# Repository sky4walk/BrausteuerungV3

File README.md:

# BrausteuerungV3
mikroSikaru.de

brausteuerung@AndreBetz.de
 
more Information found on 
https://zwieselbrau.wordpress.com/2016/03/30/mikrosikaru-brausteuerung-v3-bluetooth/

Video Tutorial
https://zwieselbrau.wordpress.com/2017/05/13/mikrosikaru-brausteuerung-v3-bedienung-videoanleitung/

Android App in Playstore:
https://play.google.com/store/apps/details?id=de.mikrosikaru.brausteuerungapp

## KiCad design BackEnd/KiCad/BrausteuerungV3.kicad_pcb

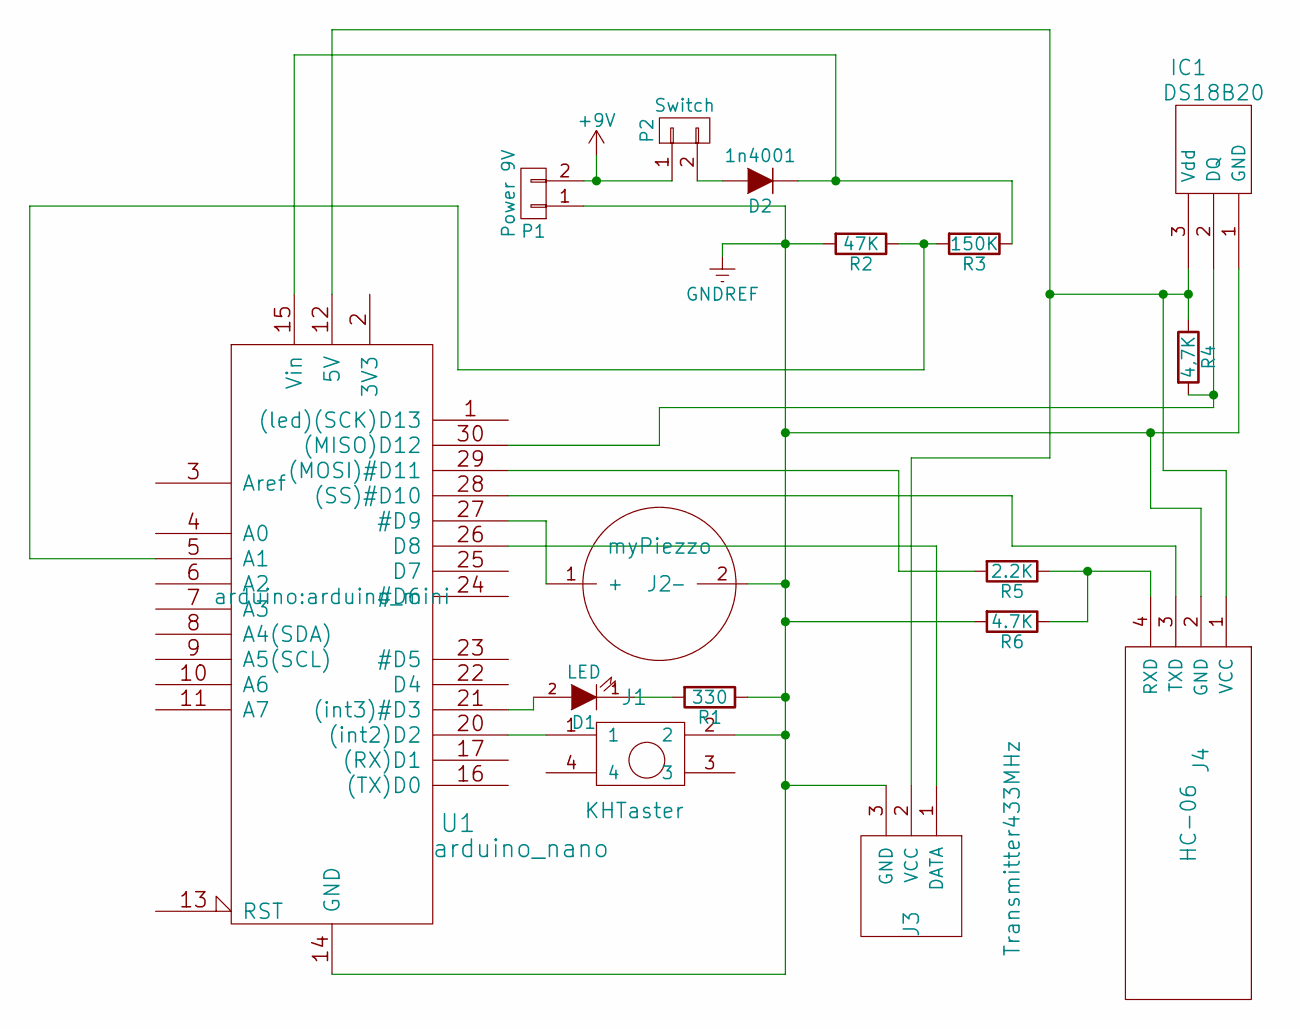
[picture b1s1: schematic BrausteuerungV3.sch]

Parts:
D1: LED; R_Axial_DIN0204_L3.6mm_D1.6mm_P1.90mm_Vertical
D2: 1n4001; R_Axial_DIN0207_L6.3mm_D2.5mm_P10.16mm_Horizontal
IC1: DS18B20
J1: KHTaster
J2: myPiezzo; PIEZZO
J3: Transmitter433MHz
J4: HC-06
P1: Power 9V; R_Axial_DIN0204_L3.6mm_D1.6mm_P1.90mm_Vertical
P2: Switch; R_Axial_DIN0204_L3.6mm_D1.6mm_P1.90mm_Vertical
R1: 330; R_Axial_DIN0207_L6.3mm_D2.5mm_P10.16mm_Horizontal
R2: 47K; R_Axial_DIN0207_L6.3mm_D2.5mm_P10.16mm_Horizontal
R3: 150K; R_Axial_DIN0207_L6.3mm_D2.5mm_P10.16mm_Horizontal
R4: 4,7K; R_Axial_DIN0207_L6.3mm_D2.5mm_P10.16mm_Horizontal
R5: 2.2K; R_Axial_DIN0207_L6.3mm_D2.5mm_P10.16mm_Horizontal
R6: 4.7K; R_Axial_DIN0207_L6.3mm_D2.5mm_P10.16mm_Horizontal
U1: arduino_nano; arduino_mini

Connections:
+9V: P1.2, P2.1
GND: U1.19 (GND)
GNDREF: IC1.1 (GND), J1.2, J2.2 (-), J3.3 (GND), J4.2 (GND), P1.1, R1.1, R2.2, R6.2, U1.14 (GND)
unnamed: D1.1 (K), R1.2
unnamed: D1.2 (A), U1.21 ((int3)#D3)
unnamed: D2.1 (K), R3.1, U1.15 (Vin)
unnamed: D2.2 (A), P2.2
unnamed: IC1.2 (DQ), R4.2, U1.30 ((MISO)D12)
unnamed: IC1.3 (Vdd), J3.2 (VCC), J4.1 (VCC), R4.1, U1.12 (5V)
unnamed: J1.1, U1.20 ((int2)D2)
unnamed: J2.1 (+), U1.27 (#D9)
unnamed: J3.1 (DATA), U1.26 (D8)
unnamed: J4.3 (TXD), U1.28 ((SS)#D10)
unnamed: J4.4 (RXD), R5.1, R6.1
unnamed: R2.1, R3.2, U1.5 (A1)
unnamed: R5.2, U1.29 ((MOSI)#D11)

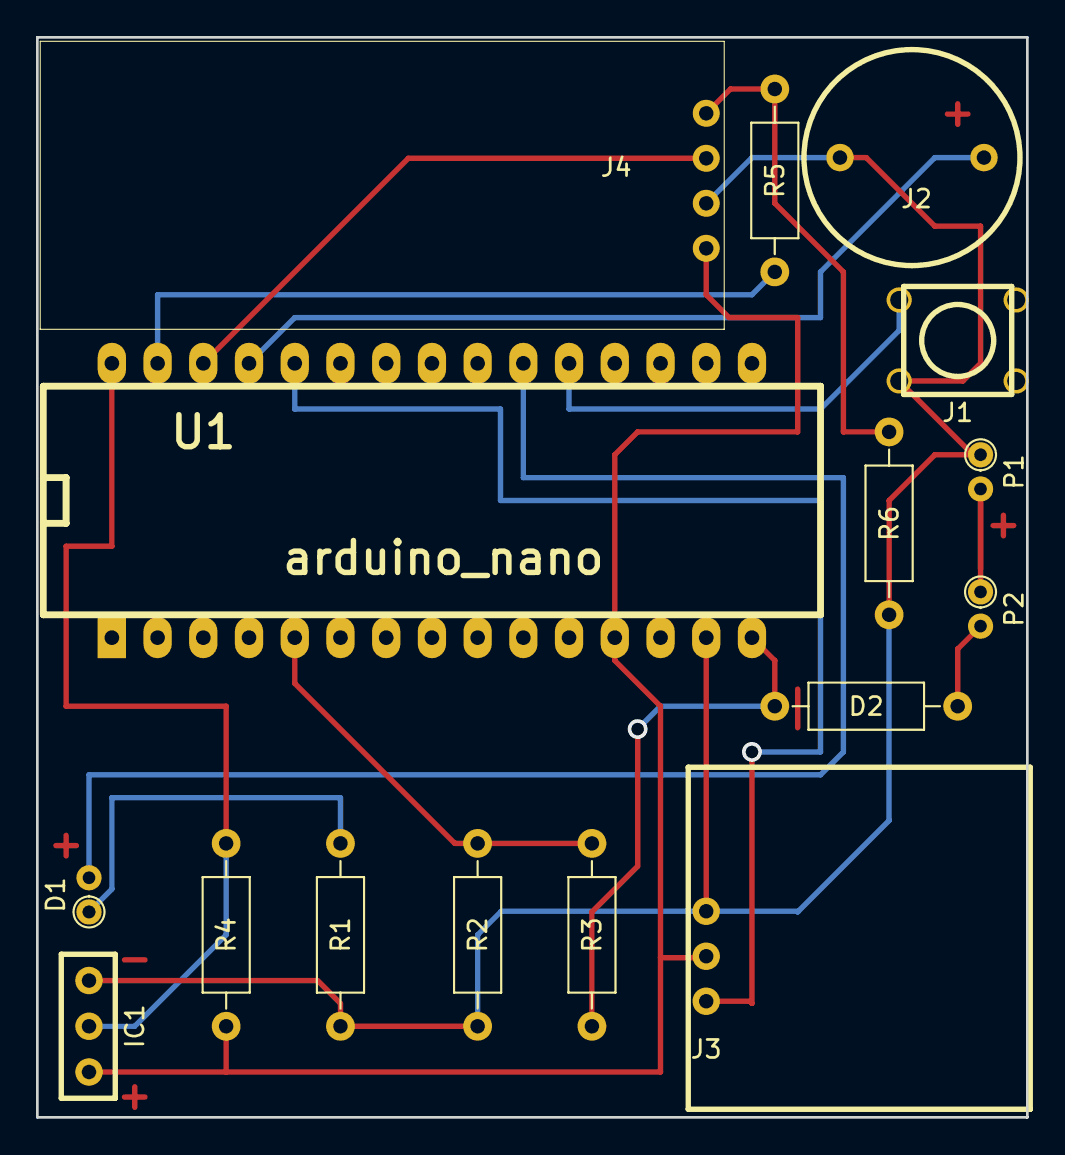
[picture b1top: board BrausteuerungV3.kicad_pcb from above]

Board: 2 copper layers, 55.0 x 60.0 mm, 16 parts (0 on the bottom side), 15 nets.

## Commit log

2016-04-25 Start BrausteuerungV3 checkin
2016-04-25 Bier Rezepte und Manual
2016-04-25 Android App
2016-04-26 version 1.3
2016-04-28 noch ein paar infos dazu
2016-04-30 Version 1.4
2016-05-18 neues angepasstes Manual
2016-05-18 version 1.5
2016-05-21 kochtemperatur beschrieben
2016-05-25 Funksteckdose einlernen
2016-05-27 http server
2016-06-20 Manual erweitert zwecks Sicherheitsinformationen
2016-07-03 version 1.7
2016-07-21 Pils Bie Rezept
2016-07-25 Pils gebraut
2016-08-07 version 1.9
2016-09-02 Zwickelbierrezept für BrausteuerungV3 App
2016-09-02 chenged some settings
2016-09-16 version 1.10
2016-12-29 new Version App 1.14 Arduini 301210
2016-12-30 changed: - temp measure timer - switch timer
2016-12-30 readme for arduino flushing new firmware
2017-01-01 Arduino: switch always off heating when not brewing Android: some thread optimizing and fixing possible race conditions
2017-01-02 added information about Windows usb2serial driver for arduino chipset
2017-01-03 driver for CH341SER
2017-01-04 some more information about downloading FW
2017-01-08 bug fix: Funksignal wurde nur bei Aenderung des Heizungszustandes geändert
2017-01-19 added download link for zip file
2017-01-27 Anleitung mit WEEE EAR Nummer
2017-02-15 Zusammenbauanleitung
2017-02-22 html manual
2017-02-22 verzeichnis geaendert
2017-02-22 changed directory
2017-04-13 added programm to set the Bluetooth device and App connection
2017-04-13 some changes in parts and Zusammenbau.pdf
2017-04-23 Rezept Fraenkisches Landbier und Brau Log
2017-05-04 fehler in widerstaenden behoben und zwei neue bilder
2017-05-15 widerstandscodierung hinzugefuegt
2017-05-22 new Firmware version and Android app
2017-06-13 new FW because if pause bug. sometimes timer stopps
2017-06-13 neues Rezept mit Log
2017-06-13 added documention - documents for building - documents for user - gerber files and kicad files for layout circuit - label document
2017-06-13 added source code: - Arduino Firmware - Android App
2017-06-22 changed calculation document
2017-07-08 neue Funksteckdose hinzugefuegt
2017-07-16 changed files
2017-07-18 Kuehlrezept fuer Brausteuerung
    ermoeglicht damit einen Kuehlschrank zu steuern fuer die Gaerfuehrung
2017-07-24 fixed some bugs in the Android App. New Version 1.19
2017-08-13 Obergaeriges Bockbier
2017-08-14 changed recipe typos
2017-09-10 braulog vom 10.9.17 obergaeriges Bockbier
2017-09-12 overheat check only works when SollTemp is other then zero
2017-09-12 new binary file
2017-09-13 bug fix overheating
2017-09-20 del file
2017-09-20 calc for bottle hight
2017-09-21 changed wort correction function
2017-09-25 reconnect ds18b20 when lost connection
2017-11-11 added version FW 301709. Solved bug in overheating wrong alarm when cooling
2017-11-15 changed pricelist
2017-11-22 added female pin headers
2017-11-23 neue kippschalter
2017-11-26 changes in brew timing according pulse recognition
2017-11-27 added a reset when waitingvfor input
2017-11-30 bug overheat
2017-12-01 new FW 09 after testing ist
2018-01-10 added voltage devider for hc-06
2018-01-10 added voltage divider KiCad
2018-01-11 added kicad layout
2018-01-11 gerber und borh dateien
2018-01-11 gerberfiles
2018-01-11 doku
2018-01-14 changed port
2018-01-30 spannunsgteiler andere widerstandswerte
2018-02-11 reverted to circuit without spannungsteiler HC06
2018-02-16 some HC-06 need a circuit leveler
2018-02-18 comment to Firmware HC-06
2018-03-07 new images for new layout
2018-03-08 neue zusammenbau anleitung
2018-03-08 widerstandswerte hinzugefuegt
2018-03-17 new HC06 with FW3.0
2018-03-18 support line endings with HC-06 V3.0
2018-03-19 supprt HC-06 with FW V3
2018-03-27 added skript for HC06 V3 install
2018-03-28 changed PID
2018-05-22 chamged user information
2018-06-04 chaned text
2018-06-06 new test version
2018-06-06 install new SW
2018-06-25 readme changed
2018-07-02 corrected resistor values
2018-07-21 added diode voltage for volatge measuring
2018-08-07 compiled android fir API 28
2018-10-20 corrected recipe
2018-11-25 new arendo funksteckdose
2019-01-06 new 433MHz codes
2019-10-03 new HC06 Term handle both Firmware versions
2019-10-03 brausteuerung should detect HC06 type
2019-10-09 added buchsenleiste
2021-01-04 Box for electronix
2021-01-04 some corrections
2021-01-05 gradient not reseted after program change and better box design
2021-12-29 a little bigger hole for DC connector
2025-08-25 when temp sensor has a failure the last value is added to gradient
2025-11-22 changed error behaviour of sensor
2025-11-24 temp val error from ds18b20 will not be hidden
2025-12-30 ds18b20 stabilisierung bei stoerung
2026-01-31 bug fix sensor read out
2026-01-31 new hex files
2026-03-23 added newer sitch lib but not integrated it
